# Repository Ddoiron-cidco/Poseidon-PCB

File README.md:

# Poseidon-PCB
PCBs for Poseidon Project

PCBs are made with Kicad 5.0

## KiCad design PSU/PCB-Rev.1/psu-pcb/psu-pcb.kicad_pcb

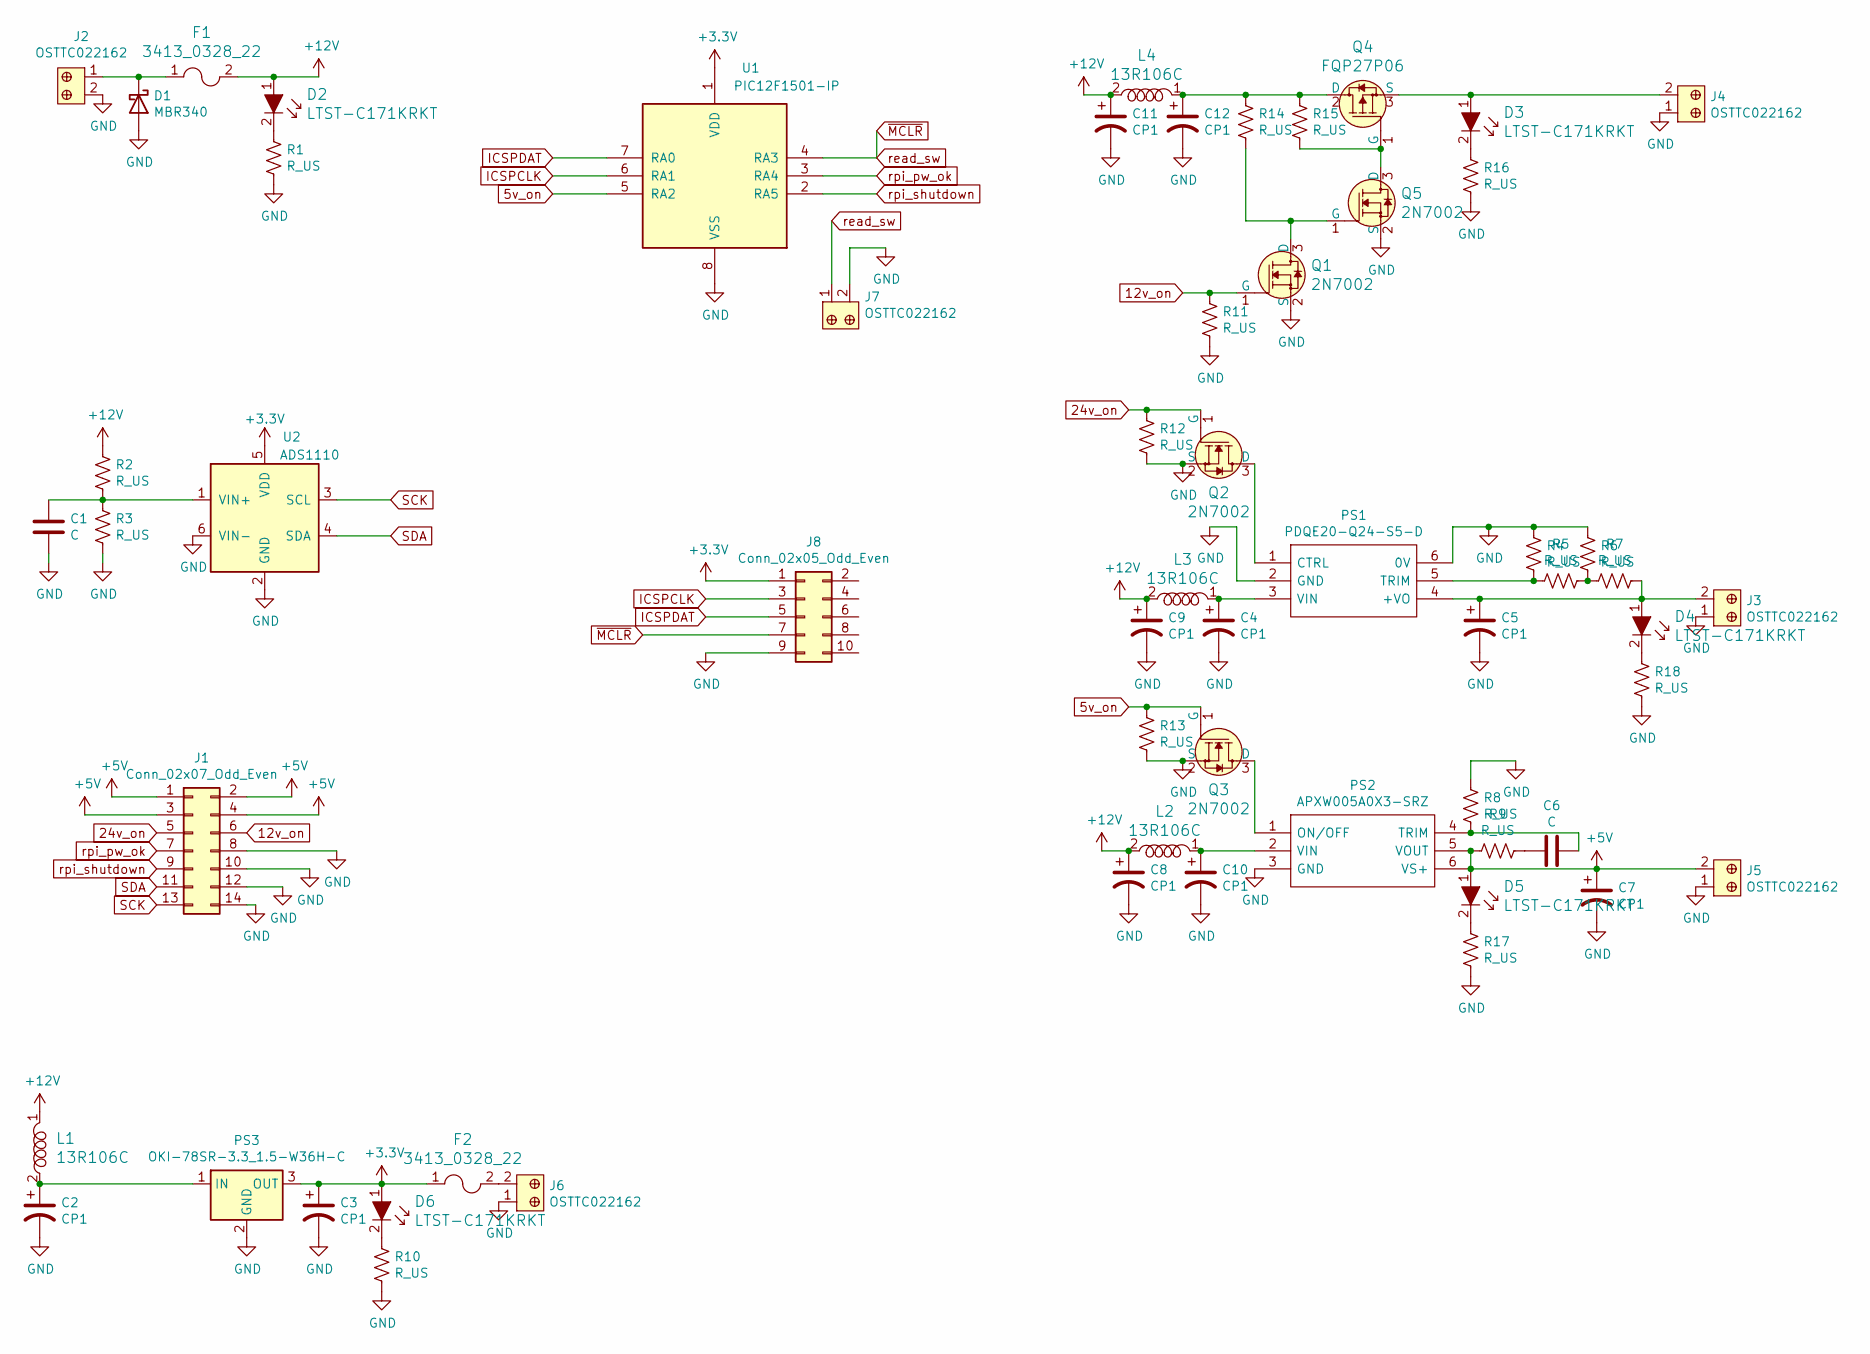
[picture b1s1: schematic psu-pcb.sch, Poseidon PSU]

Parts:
C1, C6: C; C_0805_2012Metric
C2, C3, C4, C5, C7, C8, C9, C10, C11, C12: CP1; CP_Radial_D7.5mm_P2.50mm
D1: MBR340; D_DO-201AD_P15.24mm_Horizontal
D2, D3, D4, D5, D6: LTST-C171KRKT; 0805; MPN LTST-C171KRKT; Digi-Key_PN 160-1427-1-ND
F1, F2: 3413_0328_22; 1206; MPN 3413.0328.22; Digi-Key_PN 486-1686-1-ND
J1: Conn_02x07_Odd_Even; IDC-Header_2x07_P2.54mm_Vertical_Lock
J2, J3, J4, J5, J6, J7: OSTTC022162; Term_Block_1x2_P5.08MM; MPN OSTTC022162; Digi-Key_PN ED2609-ND
J8: Conn_02x05_Odd_Even; IDC-Header_2x05_P2.54mm_Vertical
L1, L2, L3, L4: 13R106C; Inductor_13R106C; MPN 13R106C; Digi-Key_PN 811-2058-ND
PS1: PDQE20-Q24-S5-D; PDQE15Q24S5D; Manufacturer_Part_Number PDQE20-Q24-S5-D; Mouser Part Number 490-PDQE20-Q24-S5-D
PS2: APXW005A0X3-SRZ; APXW005A0X3SRZ; Manufacturer_Part_Number APXW005A0X3-SRZ; Mouser Part Number 894-APXW005A0X3-SRZ
PS3: OKI-78SR-3.3_1.5-W36H-C; Converter_DCDC_muRata_OKI-78SR_Horizontal
Q1, Q2, Q3, Q5: 2N7002; SOT-23-3; MPN 2N7002; Digi-Key_PN 2N7002NCT-ND
Q4: FQP27P06; TO-220-3; MPN FQP27P06; Digi-Key_PN FQP27P06-ND
R1, R2, R3, R4, R5, R6, R7, R8, R9, R10, R11, R12, R13, R14, R15, R16, R17, R18: R_US; R_0805_2012Metric
U1: PIC12F1501-IP; DIP-8_W7.62mm
U2: ADS1110; SOT-23-6

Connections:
5v_on: Q3.1 (G), R13.1, U1.5 (RA2)
12v_on: J1.6, Q1.1 (G), R11.1
24v_on: J1.5, Q2.1 (G), R12.1
+3V3: C3.1, D6.1, F2.1, J8.1, PS3.3 (OUT), U1.1 (VDD), U2.5 (VDD)
+5V: C7.1, D5.1, J1.1, J1.2, J1.3, J1.4, J5.2, PS2.5 (VOUT), PS2.6 (VS+), R9.1
+12V: C8.1, C9.1, C11.1, D2.1, F1.2, L1.1, L2.2, L3.2, L4.2, R2.1
GND: C1.2, C2.2, C3.2, C4.2, C5.2, C7.2, C8.2, C9.2, C10.2, C11.2, C12.2, D1.2 (A), J1.8, J1.10, J1.12, J1.14, J2.2, J3.1, J4.1, J5.1, J6.1, J7.2, J8.9, PS1.2 (GND), PS1.6 (0V), PS2.3 (GND), PS3.2 (GND), Q1.2 (S), Q2.2 (S), Q3.2 (S), Q5.2 (S), R1.2, R3.2, R4.1, R6.1, R8.2, R10.2, R11.2, R12.2, R13.2, R16.2, R17.2, R18.2, U1.8 (VSS), U2.2 (GND), U2.6 (VIN-)
ICSPCLK: J8.3, U1.6 (RA1)
ICSPDAT: J8.5, U1.7 (RA0)
unnamed: C1.1, R2.2, R3.1, U2.1 (VIN+)
unnamed: C2.1, L1.2, PS3.1 (IN)
unnamed: C4.1, L3.1, PS1.3 (VIN)
unnamed: C5.1, D4.1, J3.2, PS1.4 (+VO), R7.2
unnamed: C6.1, PS2.4 (TRIM), R8.1
unnamed: C6.2, R9.2
unnamed: C10.1, L2.1, PS2.2 (VIN)
unnamed: C12.1, L4.1, Q4.2 (D), R14.1, R15.1
unnamed: D1.1 (K), F1.1, J2.1
unnamed: D2.2, R1.1
unnamed: D3.1, J4.2, Q4.3 (S)
unnamed: D3.2, R16.1
unnamed: D4.2, R18.1
unnamed: D5.2, R17.1
unnamed: D6.2, R10.1
unnamed: F2.2, J6.2
unnamed: PS1.1 (CTRL), Q2.3 (D)
unnamed: PS1.5 (TRIM), R4.2, R5.1
unnamed: PS2.1 (ON/OFF), Q3.3 (D)
unnamed: Q1.3 (D), Q5.1 (G), R14.2
unnamed: Q4.1 (G), Q5.3 (D), R15.2
unnamed: R5.2, R6.2, R7.1
SCK: J1.13, U2.3 (SCL)
SDA: J1.11, U2.4 (SDA)
read_sw: J7.1, J8.7, U1.4 (RA3)
rpi_pw_ok: J1.7, U1.3 (RA4)
rpi_shutdown: J1.9, U1.2 (RA5)

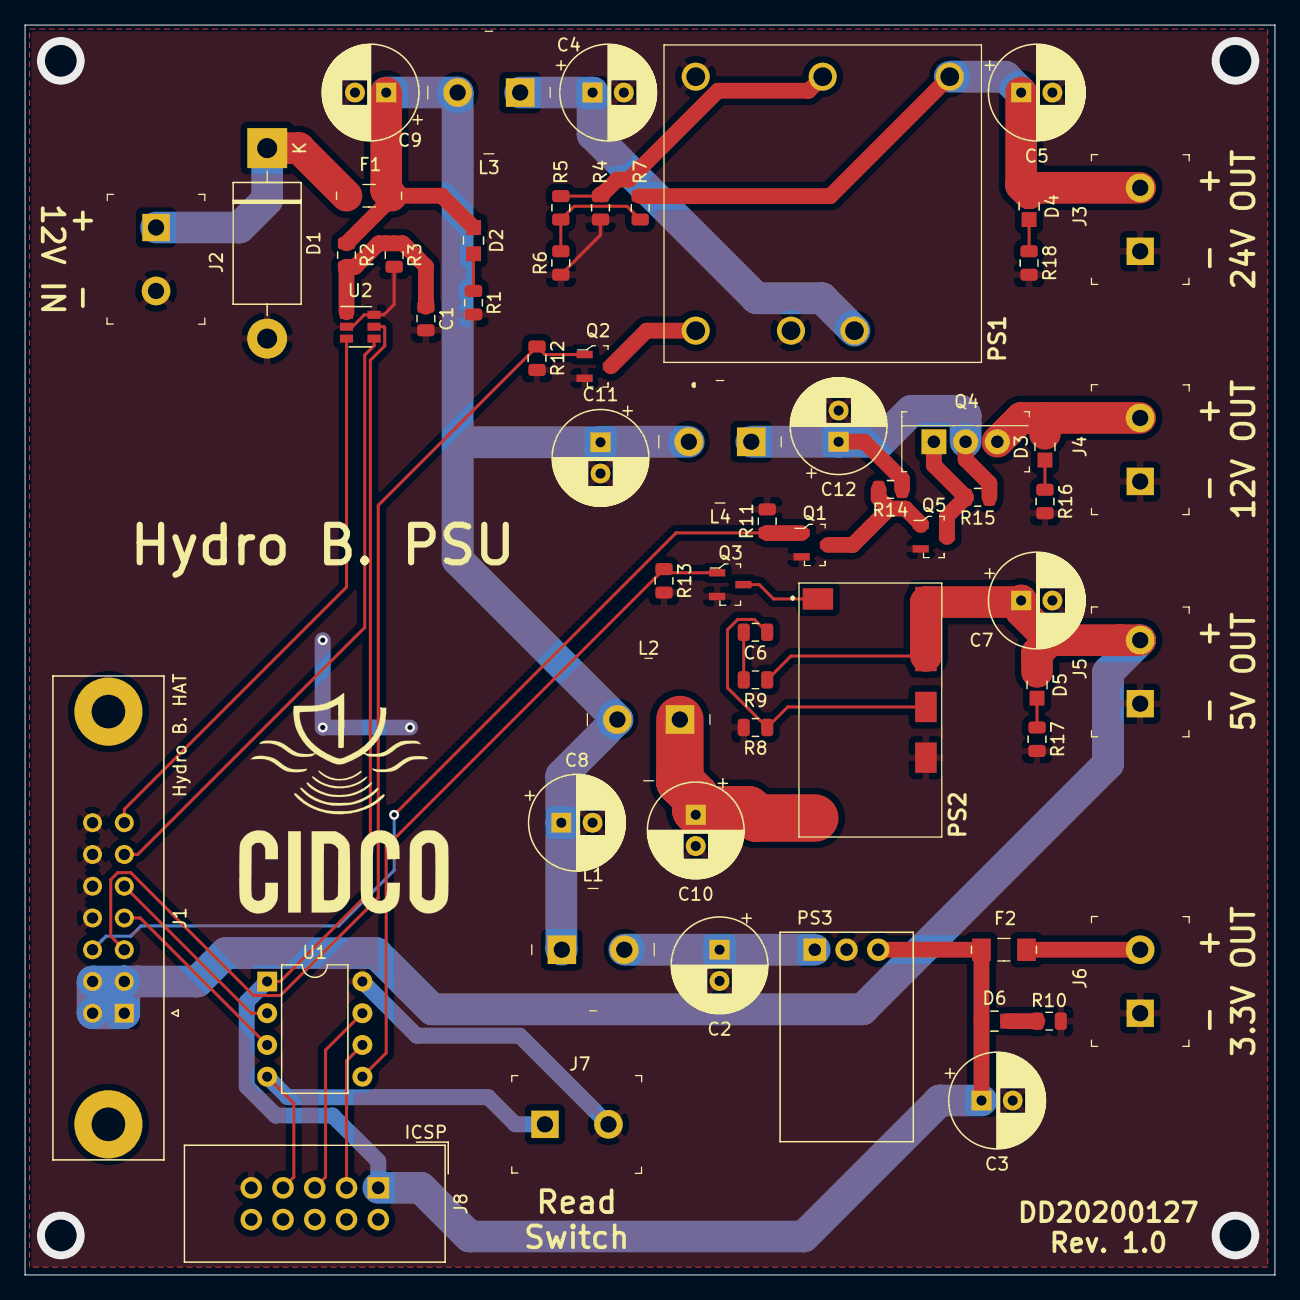
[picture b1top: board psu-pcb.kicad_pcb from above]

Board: 2 copper layers, 100.0 x 100.0 mm, 60 parts (0 on the bottom side), 36 nets.

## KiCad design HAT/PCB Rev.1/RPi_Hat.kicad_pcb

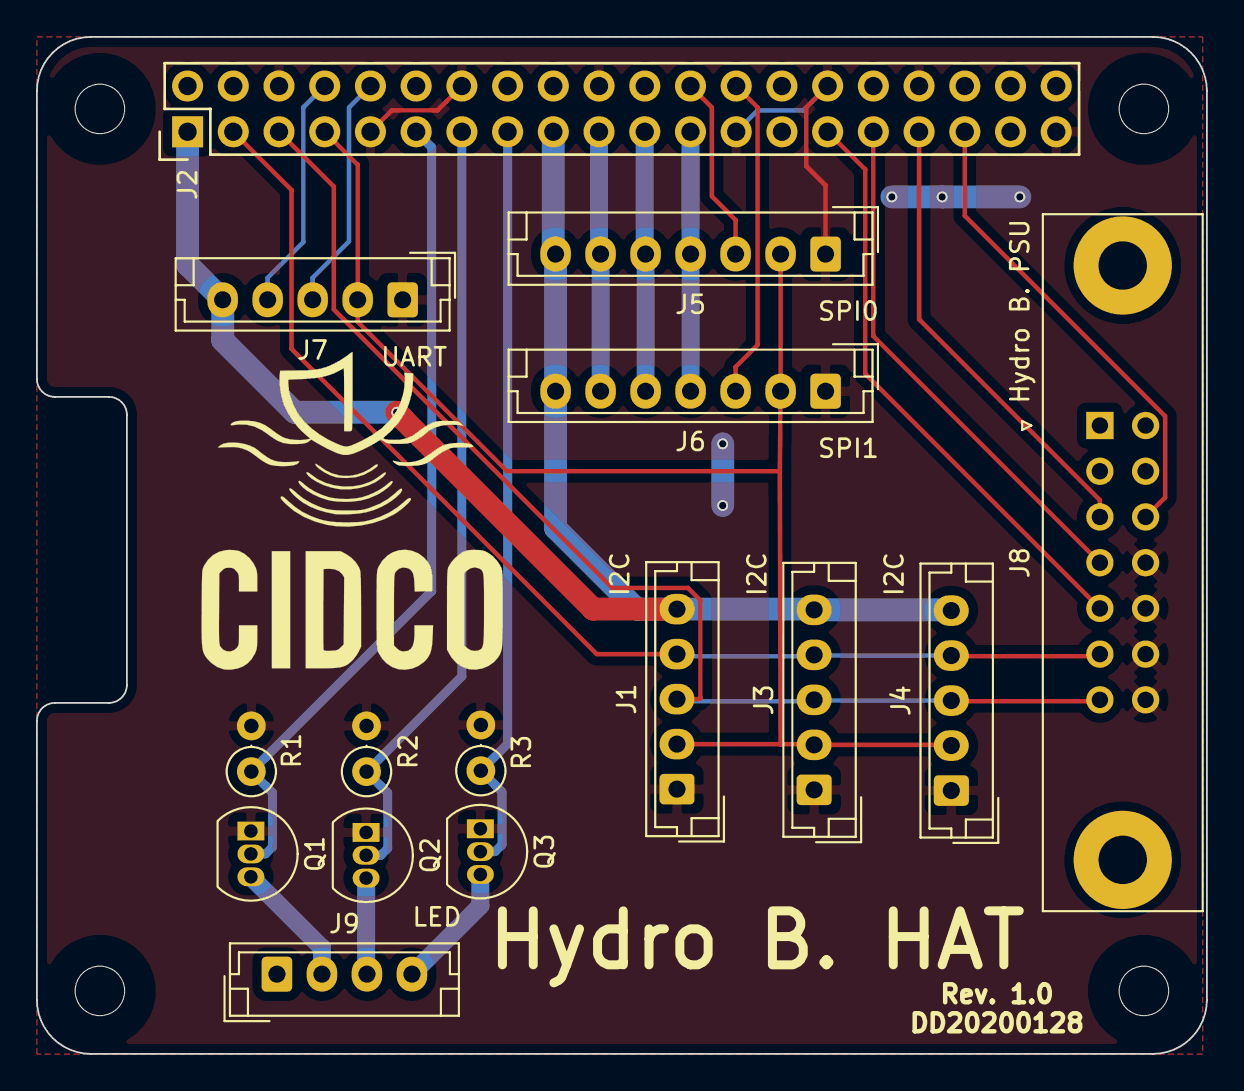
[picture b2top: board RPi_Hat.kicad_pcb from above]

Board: 2 copper layers, 65.0 x 56.5 mm, 15 parts (0 on the bottom side), 23 nets.

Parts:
J1, J3, J4, J7: Conn_01x05; JST_EH_B5B-EH-A_1x05_P2.50mm_Vertical
J2: RPi_GPIO; Pin_Header_Straight_2x20
J5, J6: Conn_01x07; JST_EH_B7B-EH-A_1x07_P2.50mm_Vertical
J8: Conn_02x07_Odd_Even; IDC-Header_2x07_P2.54mm_Vertical_Lock
J9: Conn_01x04; JST_EH_B4B-EH-A_1x04_P2.50mm_Vertical
Q1, Q2, Q3: 2N7000; TO-92_Inline
R1, R2, R3: 1k; R_Axial_DIN0207_L6.3mm_D2.5mm_P2.54mm_Vertical

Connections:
3.3V: J1.5, J2.1, J2.17, J3.5, J4.5, J5.7, J6.7, J7.5
5V: J2.2, J2.4, J8.1, J8.2, J8.3, J8.4, J9.1
12V_ON: J2.35, J8.6
24V_ON: J2.33, J8.5
C0: J2.24, J5.3
C1: J2.26, J6.3
GND: J1.1, J2.6, J2.9, J2.14, J2.20, J2.25, J2.30, J2.34, J2.39, J3.1, J4.1, J5.1, J6.1, J7.1, J8.8, J8.10, J8.12, J8.14, Q1.1, Q2.1, Q3.1, R1.2, R2.2, R3.2
LEDB: J2.15, Q3.2, R3.1
LEDG: J2.13, Q2.2, R2.1
LEDR: J2.11, Q1.2, R1.1
MISO: J2.21, J5.5, J6.5
MOSI: J2.19, J5.6, J6.6
unnamed: J9.2, Q1.3
unnamed: J9.3, Q2.3
unnamed: J9.4, Q3.3
PPS: J1.2, J2.7, J3.2, J4.2, J5.2, J6.2, J7.2
RPI_PWR_OK: J2.31, J8.7
RPI_SHDWN: J2.29, J8.9
RX: J2.10, J7.3
SCL: J1.3, J2.5, J3.3, J4.3, J8.13
SCLK: J2.23, J5.4, J6.4
SDA: J1.4, J2.3, J3.4, J4.4, J8.11
TX: J2.8, J7.4

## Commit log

2020-01-24 directory update
2020-01-27 update sch file for psu
2020-01-27 Poseidon PSU pcb
2020-01-28 schematic update
2020-01-28 psu ready to be validated
2020-01-28 update module daughter
2020-01-28 Removed submodule Daughter-board/RPi_Hat_Template
2020-01-29 photo pcb Daughter
2020-01-29 update psu and hat
2020-01-29 pcb images
2020-01-29 smt to TH
2020-01-30 update hat
2020-01-30 gerber files
2020-01-30 update BOM pour digikey
2020-06-30 ajout bornier pour supporter le rpi sur le psu

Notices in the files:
HAT/PCB Rev.1/RPi_Hat.kicad_pcb:
License: CC BY 4.0
PSU/PCB-Rev.1/psu-pcb/psu-pcb.sch:
creativecommons.org/licenses/by/4.0
